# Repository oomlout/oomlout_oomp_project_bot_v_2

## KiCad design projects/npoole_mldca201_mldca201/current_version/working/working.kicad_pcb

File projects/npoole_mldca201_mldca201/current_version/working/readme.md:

# mldca201
 
## summary 
* id: npoole_mldca201_mldca201
* user: npoole
* name: mldca201
* board: mldca201
* repo: https://github.com/NPoole/MLDCA201

* src_file_repo_sch: 
* src_file_repo_sch_link: https://github.com/NPoole/MLDCA201/tree/main/
* full details link: https://github.com/oomlout/oomlout_oomp_project_bot_v_2/tree/main/projects/npoole_mldca201_mldca201/current_version/working  

## schematic  
  
[schematic (pdf)](working_schematic.pdf) 

## pcb  

[board (pdf)](working.pdf)  

## working_bom
| Id | Designator | Footprint | Quantity | Designation | Supplier and ref |  | None | 
| --- | --- | --- | --- | --- | --- | --- | --- | 
| 1 | R35,R36,R37,R34 | 0603 | 4 | 5.1k |  |  | [''] | 
| 2 | R14,R31,R28,R25,R26,R24,R15,R27,R29,R30 | 0603 | 10 | 10k |  |  | [''] | 
| 3 | C5,C4 | 0603 | 2 | 1.0uF |  |  | [''] | 
| 4 | S19,S5,S12,S6,S4,S15,S11,S1,S22,S7,S8,S9,S14,S16,S13,S2,S18,S10,S21,S3,S17,S23,S20,S24 | CHERRY-MX-LED-1U | 24 | MECHANICAL-KEYBOARD1U |  |  | [''] | 
| 5 | D21,D2,D1,D17,D32,D15,D33,D20,D18,D16,D29,D24,D12,D9,D10,D3,D19,D34,D5,D13,D6,D11,D22,D4,D14,D8,D7,D23 | SOD-323@1 | 28 | 250mA/100V |  |  | [''] | 
| 6 | C2,C1,C3 | 0805 | 3 | 22uF |  |  | [''] | 
| 7 | U5 | QFN-44-NOPAD_1_1-LESS_PASTE | 1 | 32U4 |  |  | [''] | 
| 8 | D28,D27,D25,D26 | LED-0603@1 | 4 | RED |  |  | [''] | 
| 9 | @HOLE0 |  | 1 |  |  |  | [''] | 
| 10 | R19,R23,R17,R22,R20,R16,R18,R21 | 0603 | 8 | 20k |  |  | [''] | 
| 11 | C15,C11,C8,C16 | 0603 | 4 | 22pF |  |  | [''] | 
| 12 | R13,R1,R3 | 0603 | 3 | 100k |  |  | [''] | 
| 13 | C14 | PANASONIC_D | 1 | 100uF |  |  | [''] | 
| 14 | U$1 | ICP-10101 | 1 | ICP-10101 |  |  | [''] | 
| 15 | U2 | MSOP8 | 1 | PAM2401 |  |  | [''] | 
| 16 | U7 | SO14 | 1 | LMV324 |  |  | [''] | 
| 17 | R5,R10,R8,R7 | 0603 | 4 | 2.2k |  |  | [''] | 
| 18 | C13,C7 | 0603 | 2 | 0.1uF |  |  | [''] | 
| 19 | S28,S26,S27,S25 | TACTILE_SWITCH_SMD_5.2MM | 4 | MOMENTARY-SWITCH-SPST-SMD-5.2MM-TALL |  |  | [''] | 
| 20 | R4,R2 | 0603 | 2 | 750K |  |  | [''] | 
| 21 | R33 | 0603 | 1 | 10 |  |  | [''] | 
| 22 | D35,D31 | SOD-323 | 2 | 3A/10V/280mV |  |  | [''] | 
| 23 | C6 | 0603 | 1 | 100pF |  |  | [''] | 
| 24 | R32,R12,R9 | 0603 | 3 | 1k |  |  | [''] | 
| 25 | Y1,Y2 | CRYSTAL-SMD-2.0X1.6MM | 2 | 16MHz |  |  | [''] | 
| 26 | U1 | SOT23-5 | 1 | MCP73831 |  |  | [''] | 
| 27 | J7 | AUDIO-JACK | 1 | AUDIO_JACK_3.5MM_PTH |  |  | [''] | 
| 28 | U4 | VSSOP_8PIN | 1 |  |  |  | [''] | 
| 29 | L1 | INDUCTOR_4X4MM | 1 | 2.2UH3A |  |  | [''] | 
| 30 | C12 | 0603 | 1 | 10nF |  |  | [''] | 
| 31 | Q1 | SOT-416FL | 1 | 100mA/20V/3.8Î© |  |  | [''] | 
| 32 | C10,C9 | 0603 | 2 | 4.7uF |  |  | [''] | 
| 33 | RPROG0 | 0603 | 1 | 2.0k |  |  | [''] | 
| 34 | D30 | LED-0603@1 | 1 | BLUE |  |  | [''] | 
| 35 | J4,J2 | JST-2-SMD | 2 | JST |  |  | [''] | 
| 36 | VR1 | SLIDER-SMALL | 1 | 10k |  |  | [''] | 
| 37 | J6 | USB-C-16P-2LAYER-PADS | 1 |  |  |  | [''] | 
| 38 | FRAME1 | CREATIVE_COMMONS | 1 | FRAME-LEDGER |  |  | [''] | 
| 39 | U3 | SOT23-5 | 1 | AP2127K-1.8V |  |  | [''] | 
| 40 | R6 | 0603 | 1 | 330 |  |  | [''] | 
| 41 | S31 | SWITCH_SPST_SMD_A | 1 |  |  |  | [''] | 
| 42 | U6 | 32M1-A_ATM | 1 | ATTINY861V-10MU |  |  | [''] | 
| 43 | R11 | 0603 | 1 | 200k |  |  | [''] | 
| 44 | J3,J5 | 2X3-NS | 2 | AVR_SPI_PROG_3X2NS |  |  | [''] | 

## bom_schematic
| Ref | Qnty | Value | Cmp name | Footprint | Description | Vendor | DNP | 
| --- | --- | --- | --- | --- | --- | --- | --- | 
| C1, C2, C3 | 3 | 22UF-0805-6.3V-20% | 22UF-0805-6.3V-20% | working:0805 |  |  |  | 
| C4, C5 | 2 | 1.0UF-0603-16V-10% | 1.0UF-0603-16V-10% | working:0603 |  |  |  | 
| C6 | 1 | 100PF-0603-50V-5% | 100PF-0603-50V-5% | working:0603 |  |  |  | 
| C7, C13 | 2 | 0.1UF-0603-25V-(+80/-20%) | 0.1UF-0603-25V-(+80/-20%) | working:0603 |  |  |  | 
| C8, C11, C15, C16 | 4 | 22PF-0603-50V-5% | 22PF-0603-50V-5% | working:0603 |  |  |  | 
| C9, C10 | 2 | 4.7UF-0603-35V-(20%) | 4.7UF-0603-35V-(20%) | working:0603 |  |  |  | 
| C12 | 1 | 10NF-0603-50V-10% | 10NF-0603-50V-10% | working:0603 |  |  |  | 
| C14 | 1 | 100UF-POLAR-25V-20%(ELEC) | 100UF-POLAR-25V-20%(ELEC) | working:PANASONIC_D |  |  |  | 
| D1, D2, D3, D4, D5, D6, D7, D8, D9, D10, D11, D12, D13, D14, D15, D16, D17, D18, D19, D20, D21, D22, D23, D24, D29, D32, D33, D34 | 28 | DIODE-BAS16J | DIODE-BAS16J | working:SOD-323@1 |  |  |  | 
| D25, D26, D27, D28 | 4 | RED | LED-RED0603 | working:LED-0603@1 |  |  |  | 
| D30 | 1 | BLUE | LED-BLUE0603 | working:LED-0603@1 |  |  |  | 
| D31, D35 | 2 | 3A/10V/280mV | DIODE-SCHOTTKY-BAT60A | working:SOD-323 |  |  |  | 
| FRAME1 | 1 | FRAME-LEDGER | FRAME-LEDGER | working:CREATIVE_COMMONS |  |  |  | 
| J2, J4 | 2 | JST | CONN_02-JST-2MM-SMT | working:JST-2-SMD |  |  |  | 
| J3, J5 | 2 | AVR_SPI_PROG_3X2NS | AVR_SPI_PROG_3X2NS | working:2X3-NS |  |  |  | 
| J6 | 1 | USB_C_2-LAYER_PADS | USB_C_2-LAYER_PADS | working:USB-C-16P-2LAYER-PADS |  |  |  | 
| J7 | 1 | AUDIO_JACK_3.5MM_PTH | AUDIO_JACK_3.5MM_PTH | working:AUDIO-JACK |  |  |  | 
| L1 | 1 | INDUCTOR-IFSC1515AHER2R2M01 | INDUCTOR-IFSC1515AHER2R2M01 | working:INDUCTOR_4X4MM |  |  |  | 
| Q1 | 1 | MOSFET_PCH-RE1C001ZPTL | MOSFET_PCH-RE1C001ZPTL | working:SOT-416FL |  |  |  | 
| R1, R3, R13 | 3 | 100KOHM-0603-1/10W-1% | 100KOHM-0603-1/10W-1% | working:0603 |  |  |  | 
| R2, R4 | 2 | 750KOHM-0603-1/10W-1% | 750KOHM-0603-1/10W-1% | working:0603 |  |  |  | 
| R5, R7, R8, R10 | 4 | 2.2KOHM-0603-1/10W-1% | 2.2KOHM-0603-1/10W-1% | working:0603 |  |  |  | 
| R6 | 1 | 330OHM-0603-1/10W-1% | 330OHM-0603-1/10W-1% | working:0603 |  |  |  | 
| R9, R12, R32 | 3 | 1KOHM-0603-1/10W-1% | 1KOHM-0603-1/10W-1% | working:0603 |  |  |  | 
| R11 | 1 | 200KOHM-0603-1/10W-1% | 200KOHM-0603-1/10W-1% | working:0603 |  |  |  | 
| R14, R15, R24, R25, R26, R27, R28, R29, R30, R31 | 10 | 10KOHM-0603-1/10W-1% | 10KOHM-0603-1/10W-1% | working:0603 |  |  |  | 
| R16, R17, R18, R19, R20, R21, R22, R23 | 8 | 20KOHM-0603-1/10W-1% | 20KOHM-0603-1/10W-1% | working:0603 |  |  |  | 
| R33 | 1 | 10OHM-0603-1/10W-1% | 10OHM-0603-1/10W-1% | working:0603 |  |  |  | 
| R34, R35, R36, R37 | 4 | 5.1k | 5.1KOHM5.1KOHM-0603-1/10W-1% | working:0603 |  |  |  | 
| RPROG0 | 1 | 2.0KOHM-0603-1/10W-5% | 2.0KOHM-0603-1/10W-5% | working:0603 |  |  |  | 
| S1, S2, S3, S4, S5, S6, S7, S8, S9, S10, S11, S12, S13, S14, S15, S16, S17, S18, S19, S20, S21, S22, S23, S24 | 24 | MECHANICAL-KEYBOARD1U | MECHANICAL-KEYBOARD1U | working:CHERRY-MX-LED-1U |  |  |  | 
| S25, S26, S27, S28 | 4 | MOMENTARY-SWITCH-SPST-SMD-5.2MM-TALL | MOMENTARY-SWITCH-SPST-SMD-5.2MM-TALL | working:TACTILE_SWITCH_SMD_5.2MM |  |  |  | 
| S31 | 1 | SWITCH-SPDT-SMD-RIGHT-ANGLE | SWITCH-SPDT-SMD-RIGHT-ANGLE | working:SWITCH_SPST_SMD_A |  |  |  | 
| U1 | 1 | MCP73831 | MCP73831 | working:SOT23-5 |  |  |  | 
| U2 | 1 | PAM2401 | PAM2401 | working:MSOP8 |  |  |  | 
| U3 | 1 | V_REG_AP2127K-1.8V | V_REG_AP2127K-1.8V | working:SOT23-5 |  |  |  | 
| U4 | 1 | PCA9306VSSOP_8PIN | PCA9306VSSOP_8PIN | working:VSSOP_8PIN |  |  |  | 
| U5 | 1 | ATMEGA32U41:1-LESS_PASTE | ATMEGA32U41{colon}1-LESS_PASTE | working:QFN-44-NOPAD_1_1-LESS_PASTE |  |  |  | 
| U6 | 1 | ATTINY861V-10MU | ATTINY861V-10MU | working:32M1-A_ATM |  |  |  | 
| U7 | 1 | LMV324 | LMV324 | working:SO14 |  |  |  | 
| U$1 | 1 | ICP-10101 | ICP-10101 | working:ICP-10101 |  |  |  | 
| VR1 | 1 | 10k | POTENTIOMETER_SLIDE-20MM-1/10W-20% | working:SLIDER-SMALL |  |  |  | 
| Y1, Y2 | 2 | 16MHz | CRYSTAL-16MHZSMD-2X1.6 | working:CRYSTAL-SMD-2.0X1.6MM |  |  |  |

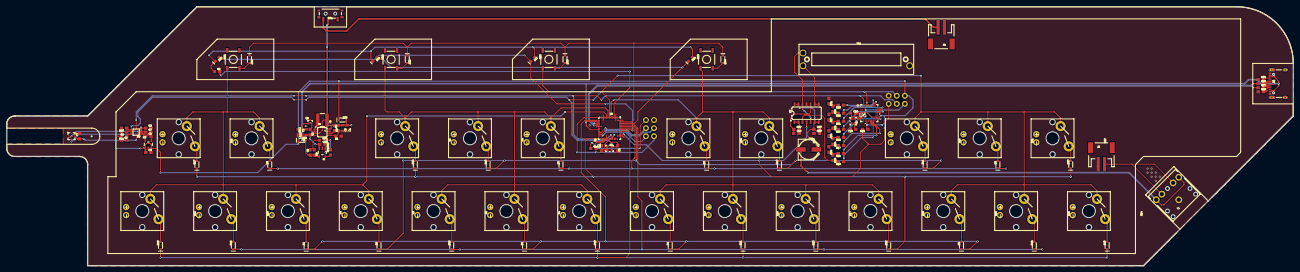
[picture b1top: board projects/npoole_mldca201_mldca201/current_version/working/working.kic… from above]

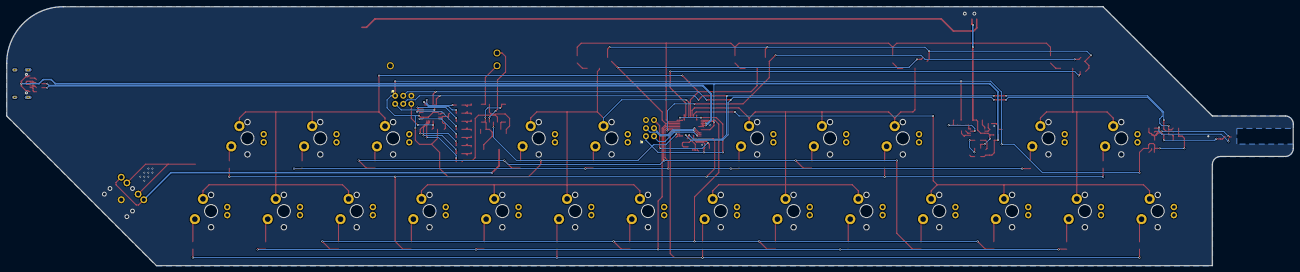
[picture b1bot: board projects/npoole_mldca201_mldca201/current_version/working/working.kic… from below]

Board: 2 copper layers, 403.9 x 81.3 mm, 139 parts (2 on the bottom side), 103 nets.

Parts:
@HOLE0: (no value)
C1, C2, C3: 22uF; 0805
C4, C5: 1.0uF; 0603
C6: 100pF; 0603
C7, C13: 0.1uF; 0603
C8, C11, C15, C16: 22pF; 0603
C9, C10: 4.7uF; 0603
C12: 10nF; 0603
C14: 100uF; PANASONIC_D
D1, D2, D3, D4, D5, D6, D7, D8, D9, D10, D11, D12, D13, D14, D15, D16, D17, D18, D19, D20, D21, D22, D23, D24, D29, D32, D33, D34: 250mA/100V; SOD-323@1
D25, D26, D27, D28: RED; LED-0603@1
D30: BLUE; LED-0603@1
D31, D35: 3A/10V/280mV; SOD-323
FRAME1: FRAME-LEDGER; CREATIVE_COMMONS
J2, J4: JST; JST-2-SMD
J3, J5: AVR_SPI_PROG_3X2NS; 2X3-NS
J6: USB-C-16P-2LAYER-PADS
J7: AUDIO_JACK_3.5MM_PTH; AUDIO-JACK
L1: 2.2UH3A; INDUCTOR_4X4MM
Q1: 100mA/20V/3.8Ω; SOT-416FL
R1, R3, R13: 100k; 0603
R2, R4: 750K; 0603
R5, R7, R8, R10: 2.2k; 0603
R6: 330; 0603
R9, R12, R32: 1k; 0603
R11: 200k; 0603
R14, R15, R24, R25, R26, R27, R28, R29, R30, R31: 10k; 0603
R16, R17, R18, R19, R20, R21, R22, R23: 20k; 0603
R33: 10; 0603
R34, R35, R36, R37: 5.1k; 0603
RPROG0: 2.0k; 0603
S1, S2, S3, S4, S5, S6, S7, S8, S9, S10, S11, S12, S13, S14, S15, S16, S17, S18, S19, S20, S21, S22, S23, S24: MECHANICAL-KEYBOARD1U; CHERRY-MX-LED-1U
S25, S26, S27, S28: MOMENTARY-SWITCH-SPST-SMD-5.2MM-TALL; TACTILE_SWITCH_SMD_5.2MM
S31: SWITCH_SPST_SMD_A
U1: MCP73831; SOT23-5
U2: PAM2401; MSOP8
U3: AP2127K-1.8V; SOT23-5
U4: VSSOP_8PIN
U5: 32U4; QFN-44-NOPAD_1_1-LESS_PASTE
U6: ATTINY861V-10MU; 32M1-A_ATM
U7: LMV324; SO14
U$1: ICP-10101
VR1: 10k; SLIDER-SMALL
Y1, Y2: 16MHz; CRYSTAL-SMD-2.0X1.6MM

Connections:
1.8V: C5.1, C7.1, R5.2, R7.2, U3.5, U4.P2, U$1.5, U$1.6, U$1.10
5V: C4.1, D31.C, D35.C, J3.2, J5.2, R8.2, R10.2, R11.2, R14.2, R15.2, U3.1, U3.3, U5.14, U5.24, U5.34, U5.44, U6.4, U6.18, U7.4
32U4_CIPO: J5.1, U5.11
32U4_COPI: J5.4, U5.10
32U4_SCK: J5.3, U5.9
861CIPO: J3.1, U6.31
AUDIO_OUT: C14.-, J7.RING, J7.TIP
COL1: D1.C, D2.C, D3.C, D4.C, U5.1
COL2: D5.C, D6.C, D7.C, D8.C, U5.28
COL3: D9.C, D10.C, D11.C, D12.C, U5.29
COL4: D13.C, D14.C, D15.C, D16.C, U5.30
COL5: D17.C, D22.C, D23.C, D24.C, U5.12
COL6: D18.C, D19.C, D20.C, D21.C, U5.26
COL7: D29.C, D32.C, D33.C, D34.C, U5.32
DAC_0: R23.1, U6.26
DAC_1: R22.1, U6.25
DAC_2: R21.1, U6.23
DAC_3: R20.1, U6.22
DAC_4: R18.1, U6.17
DAC_5: R17.1, U6.15
DAC_6: R16.1, U6.14
DAC_7: R19.1, U6.13
DAC_OUT: R19.2, R29.2, U7.3
EN: Q1.2, R2.1, U2.2
GND: C1.2, C2.2, C3.2, C4.2, C5.2, C6.1, C7.2, C8.2, C9.2, C10.2, C11.2, C12.2, C15.2, C16.2, J2.1, J3.6, J4.1, J5.6, J6.GND, J6.GND2, J7.SLEEVE, Q1.3, R1.1, R3.1, R13.2, R31.1, R33.1, R34.1, R35.1, RPROG0.2, U1.2, U2.4, U2.8, U3.2, U4.P1, U5.5, U5.15, U5.23, U5.33, U5.35, U5.43, U6.5, U6.21, U7.11, U$1.3, U$1.8, U$1.9, VR1.BOTTOM
LED0: R6.2, U5.36
LED1: D26.A, D28.C, U5.31
LED2: D25.A, D27.C, U5.27
unnamed: RPROG0.1, U1.5
unnamed: D30.C, U1.1
unnamed: J4.2, S31.1
unnamed: D30.A, R9.1
unnamed: D1.A, S8.S2
unnamed: D2.A, S1.S2
unnamed: D3.A, S20.S2
unnamed: D4.A, S13.S2
unnamed: D5.A, S14.S2
unnamed: D6.A, S21.S2
unnamed: D7.A, S2.S2
unnamed: D8.A, S9.S2
unnamed: D9.A, S3.S2
unnamed: D10.A, S4.S2
unnamed: D11.A, S15.S2
unnamed: D12.A, S16.S2
unnamed: D13.A, S17.S2
unnamed: D14.A, S22.S2
unnamed: D15.A, S5.S2
unnamed: D16.A, S10.S2
unnamed: D17.A, S11.S2
unnamed: D24.A, S6.S2
unnamed: D23.A, S23.S2
unnamed: D22.A, S18.S2
unnamed: D21.A, S19.S2
unnamed: D20.A, S24.S2
unnamed: D19.A, S7.S2
unnamed: D18.A, S12.S2
unnamed: R1.2, R4.1, U2.5
unnamed: L1.P$2, U2.1
unnamed: R3.2, U2.6
unnamed: D29.A, S25.3
unnamed: D32.A, S26.3
unnamed: Q1.1, R12.2, R13.1
unnamed: D33.A, S27.3
unnamed: D34.A, S28.3
unnamed: D25.C, D26.C, D27.A, D28.A, R6.1
unnamed: C6.2, R11.1, U4.P7, U4.P8
unnamed: C1.1, C2.1, D35.A, R4.2, U2.7
unnamed: C11.1, U5.16, Y2.1
unnamed: C8.1, U5.17, Y2.3
unnamed: U7.8, U7.9, VR1.TOP
unnamed: R16.2, R28.2, R29.1
unnamed: R17.2, R24.2, R28.1
unnamed: R18.2, R24.1, R25.2
unnamed: R20.2, R25.1, R26.2
unnamed: R21.2, R26.1, R27.2
unnamed: R22.2, R27.1, R30.2
unnamed: R23.2, R30.1, R31.2
unnamed: R32.2, U7.1, U7.2
unnamed: C12.1, R32.1, U7.10
unnamed: U7.5, U7.12, VR1.WIPER
unnamed: C13.1, C14.+, U7.6, U7.7, U7.13, U7.14
unnamed: C13.2, R33.2
unnamed: J6.A5, R35.2
unnamed: J6.B5, R34.2
unnamed: J6.A6, J6.B6, R36.2
unnamed: J6.A7, J6.B7, R37.2
unnamed: C16.1, U6.7, Y1.1
unnamed: C15.1, U6.8, Y1.3
unnamed: J2.2, J7.RSH, J7.TSH
ROW1: S3.S1, S8.S1, S9.S1, S10.S1, S11.S1, S12.S1, S25.1, U5.41
ROW2: S1.S1, S2.S1, S4.S1, S5.S1, S6.S1, S7.S1, S26.1, U5.40
ROW3: S15.S1, S20.S1, S21.S1, S22.S1, S23.S1, S24.S1, S27.1, U5.39
ROW4: S13.S1, S14.S1, S16.S1, S17.S1, S18.S1, S19.S1, S28.1, U5.38
SCL1_8: R7.1, U4.P3, U$1.2
SCL5: J3.3, R8.1, U4.P6, U5.18, U6.32
SDA1_8: R5.1, U4.P4, U$1.4
SDA5: J3.4, R10.1, U4.P5, U5.19, U6.30
USB_N: R37.1, U5.3
USB_P: R36.1, U5.4
VBATT: C3.1, C10.1, L1.P$1, R2.2, S31.2, U1.3, U2.3
VUSB: C9.1, D31.A, J6.VBUS1, J6.VBUS2, R9.2, R12.1, U1.4, U5.2, U5.7
~32U4_RESET: J5.5, R14.1, U5.13
~861RESET: J3.5, R15.1, U6.11

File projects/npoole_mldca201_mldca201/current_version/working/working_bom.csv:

"Id";"Designator";"Footprint";"Quantity";"Designation";"Supplier and ref";
1;"R35,R36,R37,R34";"0603";4;"5.1k";;;
2;"R14,R31,R28,R25,R26,R24,R15,R27,R29,R30";"0603";10;"10k";;;
3;"C5,C4";"0603";2;"1.0uF";;;
4;"S19,S5,S12,S6,S4,S15,S11,S1,S22,S7,S8,S9,S14,S16,S13,S2,S18,S10,S21,S3,S17,S23,S20,S24";"CHERRY-MX-LED-1U";24;"MECHANICAL-KEYBOARD1U";;;
5;"D21,D2,D1,D17,D32,D15,D33,D20,D18,D16,D29,D24,D12,D9,D10,D3,D19,D34,D5,D13,D6,D11,D22,D4,D14,D8,D7,D23";"SOD-323@1";28;"250mA/100V";;;
6;"C2,C1,C3";"0805";3;"22uF";;;
7;"U5";"QFN-44-NOPAD_1_1-LESS_PASTE";1;"32U4";;;
8;"D28,D27,D25,D26";"LED-0603@1";4;"RED";;;
9;"@HOLE0";"";1;"";;;
10;"R19,R23,R17,R22,R20,R16,R18,R21";"0603";8;"20k";;;
11;"C15,C11,C8,C16";"0603";4;"22pF";;;
12;"R13,R1,R3";"0603";3;"100k";;;
13;"C14";"PANASONIC_D";1;"100uF";;;
14;"U$1";"ICP-10101";1;"ICP-10101";;;
15;"U2";"MSOP8";1;"PAM2401";;;
16;"U7";"SO14";1;"LMV324";;;
17;"R5,R10,R8,R7";"0603";4;"2.2k";;;
18;"C13,C7";"0603";2;"0.1uF";;;
19;"S28,S26,S27,S25";"TACTILE_SWITCH_SMD_5.2MM";4;"MOMENTARY-SWITCH-SPST-SMD-5.2MM-TALL";;;
20;"R4,R2";"0603";2;"750K";;;
21;"R33";"0603";1;"10";;;
22;"D35,D31";"SOD-323";2;"3A/10V/280mV";;;
23;"C6";"0603";1;"100pF";;;
24;"R32,R12,R9";"0603";3;"1k";;;
25;"Y1,Y2";"CRYSTAL-SMD-2.0X1.6MM";2;"16MHz";;;
26;"U1";"SOT23-5";1;"MCP73831";;;
27;"J7";"AUDIO-JACK";1;"AUDIO_JACK_3.5MM_PTH";;;
28;"U4";"VSSOP_8PIN";1;"";;;
29;"L1";"INDUCTOR_4X4MM";1;"2.2UH3A";;;
30;"C12";"0603";1;"10nF";;;
31;"Q1";"SOT-416FL";1;"100mA/20V/3.8Ω";;;
32;"C10,C9";"0603";2;"4.7uF";;;
33;"RPROG0";"0603";1;"2.0k";;;
34;"D30";"LED-0603@1";1;"BLUE";;;
35;"J4,J2";"JST-2-SMD";2;"JST";;;
36;"VR1";"SLIDER-SMALL";1;"10k";;;
37;"J6";"USB-C-16P-2LAYER-PADS";1;"";;;
38;"FRAME1";"CREATIVE_COMMONS";1;"FRAME-LEDGER";;;
39;"U3";"SOT23-5";1;"AP2127K-1.8V";;;
40;"R6";"0603";1;"330";;;
41;"S31";"SWITCH_SPST_SMD_A";1;"";;;
42;"U6";"32M1-A_ATM";1;"ATTINY861V-10MU";;;
43;"R11";"0603";1;"200k";;;
44;"J3,J5";"2X3-NS";2;"AVR_SPI_PROG_3X2NS";;;

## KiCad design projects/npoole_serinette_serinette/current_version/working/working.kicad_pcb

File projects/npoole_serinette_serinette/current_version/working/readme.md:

# serinette
 
## summary 
* id: npoole_serinette_serinette
* user: npoole
* name: serinette
* board: serinette
* repo: https://github.com/NPoole/Serinette

* src_file_repo_sch: 
* src_file_repo_sch_link: https://github.com/NPoole/Serinette/tree/main/
* full details link: https://github.com/oomlout/oomlout_oomp_project_bot_v_2/tree/main/projects/npoole_serinette_serinette/current_version/working  

## schematic  
  
[schematic (pdf)](working_schematic.pdf) 

## pcb  

[board (pdf)](working.pdf)  

## working_bom
| Id | Designator | Footprint | Quantity | Designation | Supplier and ref |  | None | 
| --- | --- | --- | --- | --- | --- | --- | --- | 
| 1 | U15,U13,U9,U2,U3,U7,U1,U6,U11,U4,U5,U10,U8,U14,U12 | ALS-PT19 | 15 | LIGHT_SENSORALS |  |  | [''] | 
| 2 | S3,S2,S1,S4 | TACTILE_SWITCH_SMD_5.2MM | 4 | MOMENTARY-SWITCH-SPST-SMD-5.2MM-TALL |  |  | [''] | 
| 3 | C3,C6 | 0603 | 2 | 4.7uF |  |  | [''] | 
| 4 | @HOLE5,@HOLE2,@HOLE3,@HOLE14,@HOLE7,@HOLE8,@HOLE11,@HOLE6,@HOLE1,@HOLE0,@HOLE4,@HOLE9,@HOLE12,@HOLE13,@HOLE10 |  | 15 |  |  |  | [''] | 
| 5 | LS1 | BUZZER_SMD | 1 | BUZZER-SMD-SQUARE |  |  | [''] | 
| 6 | C1,C2 | 0603 | 2 | 1.0uF |  |  | [''] | 
| 7 | R17 | 0603 | 1 | 10k |  |  | [''] | 
| 8 | C5 | 0603 | 1 | 2.2uF |  |  | [''] | 
| 9 | C4 | 0603 | 1 | 0.1uF |  |  | [''] | 
| 10 | E$1 | KIKKERLAND15 | 1 |  |  |  | [''] | 
| 11 | OLED1 | OLED-UG-2832TSWGG01-REAR | 1 | 32x128 OLED |  |  | [''] | 
| 12 | R16 | 0603 | 1 | 560K |  |  | [''] | 
| 13 | J1 | USB-C-16P-2LAYER-PADS | 1 |  |  |  | [''] | 
| 14 | FRAME1 | CREATIVE_COMMONS | 1 | FRAME-LETTER |  |  | [''] | 
| 15 | D6,D2,D12,D4,D10,D15,D5,D11,D8,D3,D9,D14,D1,D7,D13 | LED-0603 | 15 |  |  |  | [''] | 
| 16 | R13,R8,R11,R3,R5,R4,R15,R9,R2,R1,R7,R10,R6,R14,R12 | 0603 | 15 | 330 |  |  | [''] | 

## bom_schematic
| Ref | Qnty | Value | Cmp name | Footprint | Description | Vendor | DNP | 
| --- | --- | --- | --- | --- | --- | --- | --- | 
| C1, C2 | 2 | 1.0UF-0603-16V-10% | 1.0UF-0603-16V-10% | working:0603 |  |  |  | 
| C3, C6 | 2 | 4.7UF-0603-35V-(20%) | 4.7UF-0603-35V-(20%) | working:0603 |  |  |  | 
| C4 | 1 | 0.1UF-0603-100V-10% | 0.1UF-0603-100V-10% | working:0603 |  |  |  | 
| C5 | 1 | 2.2UF-0603-10V-20% | 2.2UF-0603-10V-20% | working:0603 |  |  |  | 
| D1, D2, D3, D4, D5, D6, D7, D8, D9, D10, D11, D12, D13, D14, D15 | 15 | LED0603 | LED0603 | working:LED-0603 |  |  |  | 
| FRAME1 | 1 | FRAME-LETTER | FRAME-LETTER | working:CREATIVE_COMMONS |  |  |  | 
| J1 | 1 | USB_C_2-LAYER_PADS | USB_C_2-LAYER_PADS | working:USB-C-16P-2LAYER-PADS |  |  |  | 
| LS1 | 1 | BUZZER-SMD-SQUARE | BUZZER-SMD-SQUARE | working:BUZZER_SMD |  |  |  | 
| OLED1 | 1 | OLED128X64SIDEREAR-MOUNT | OLED128X64SIDEREAR-MOUNT | working:OLED-UG-2832TSWGG01-REAR |  |  |  | 
| R1, R2, R3, R4, R5, R6, R7, R8, R9, R10, R11, R12, R13, R14, R15 | 15 | 330OHM-0603-1/10W-1% | 330OHM-0603-1/10W-1% | working:0603 |  |  |  | 
| R16 | 1 | 750KOHM-0603-1/10W-1% | 750KOHM-0603-1/10W-1% | working:0603 |  |  |  | 
| R17 | 1 | 10KOHM-0603-1/10W-1% | 10KOHM-0603-1/10W-1% | working:0603 |  |  |  | 
| S1, S2, S3, S4 | 4 | MOMENTARY-SWITCH-SPST-SMD-5.2MM-TALL | MOMENTARY-SWITCH-SPST-SMD-5.2MM-TALL | working:TACTILE_SWITCH_SMD_5.2MM |  |  |  | 
| U1, U2, U3, U4, U5, U6, U7, U8, U9, U10, U11, U12, U13, U14, U15 | 15 | LIGHT_SENSORALS | LIGHT_SENSORALS | working:ALS-PT19 |  |  |  | 
| U16 | 1 | ATMEGA32U4-ARDUINO1:1-LESS_PASTE | ATMEGA32U4-ARDUINO1{colon}1-LESS_PASTE | working:QFN-44-NOPAD_1_1-LESS_PASTE |  |  |  |

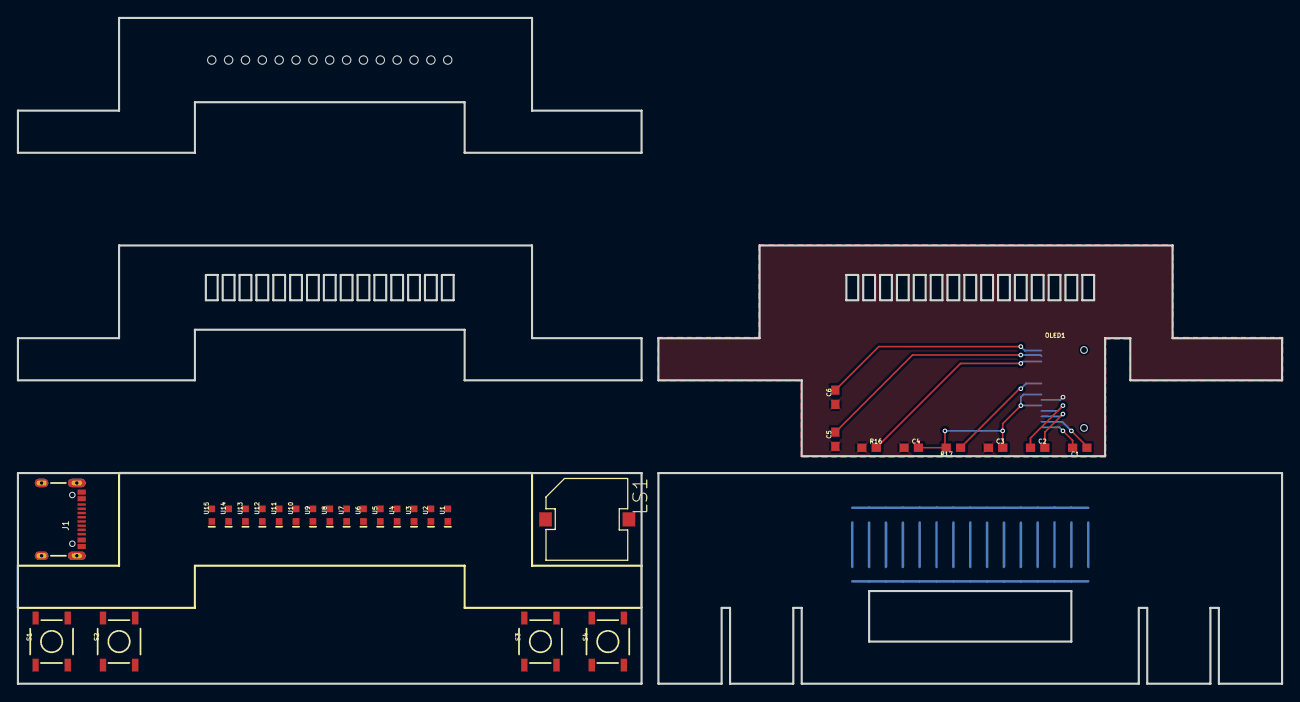
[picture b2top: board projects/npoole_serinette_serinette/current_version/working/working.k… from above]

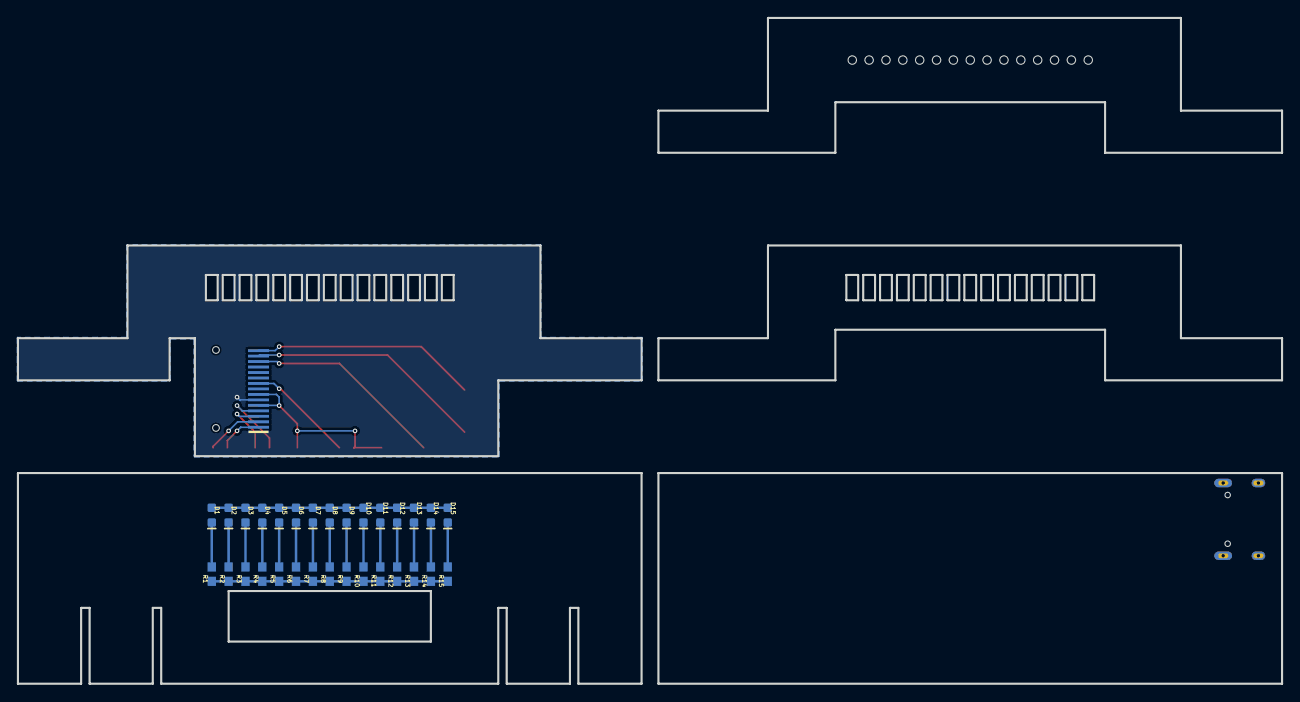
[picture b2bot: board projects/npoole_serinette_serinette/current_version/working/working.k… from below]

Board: 2 copper layers, 150.0 x 79.0 mm, 77 parts (30 on the bottom side), 27 nets.

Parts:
@HOLE0, @HOLE1, @HOLE2, @HOLE3, @HOLE4, @HOLE5, @HOLE6, @HOLE7, @HOLE8, @HOLE9, @HOLE10, @HOLE11, @HOLE12, @HOLE13, @HOLE14: (no value)
C1, C2: 1.0uF; 0603
C3, C6: 4.7uF; 0603
C4: 0.1uF; 0603
C5: 2.2uF; 0603
D1, D2, D3, D4, D5, D6, D7, D8, D9, D10, D11, D12, D13, D14, D15: LED-0603
E$1: KIKKERLAND15
FRAME1: FRAME-LETTER; CREATIVE_COMMONS
J1: USB-C-16P-2LAYER-PADS
LS1: BUZZER-SMD-SQUARE; BUZZER_SMD
OLED1: 32x128 OLED; OLED-UG-2832TSWGG01-REAR
R1, R2, R3, R4, R5, R6, R7, R8, R9, R10, R11, R12, R13, R14, R15: 330; 0603
R16: 560K; 0603
R17: 10k; 0603
S1, S2, S3, S4: MOMENTARY-SWITCH-SPST-SMD-5.2MM-TALL; TACTILE_SWITCH_SMD_5.2MM
U1, U2, U3, U4, U5, U6, U7, U8, U9, U10, U11, U12, U13, U14, U15: LIGHT_SENSORALS; ALS-PT19

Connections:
3.3V: C3.2, C4.2, OLED1.5, OLED1.7, R17.2
GND: C3.1, C4.1, C5.1, C6.1, OLED1.6, R16.1
unnamed: D1.C, R1.2
unnamed: D2.C, R2.2
unnamed: D3.C, R3.2
unnamed: D4.C, R4.2
unnamed: D5.C, R5.2
unnamed: D6.C, R6.2
unnamed: D7.C, R7.2
unnamed: D8.C, R8.2
unnamed: D9.C, R9.2
unnamed: D10.C, R10.2
unnamed: D11.C, R11.2
unnamed: D12.C, R12.2
unnamed: D13.C, R13.2
unnamed: D14.C, R14.2
unnamed: D15.C, R15.2
unnamed: R1.1, R2.1, R3.1, R4.1, R5.1, R6.1, R7.1, R8.1, R9.1, R10.1, R11.1, R12.1, R13.1, R14.1, R15.1
unnamed: D1.A, D2.A, D3.A, D4.A, D5.A, D6.A, D7.A, D8.A, D9.A, D10.A, D11.A, D12.A, D13.A, D14.A, D15.A
unnamed: C1.2, OLED1.1
unnamed: C2.2, OLED1.3
unnamed: C1.1, OLED1.2
unnamed: C2.1, OLED1.4
unnamed: OLED1.13, R16.2
unnamed: C5.2, OLED1.14
unnamed: C6.2, OLED1.15
OLED_RST: OLED1.9, R17.1

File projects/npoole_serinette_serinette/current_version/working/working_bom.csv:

"Id";"Designator";"Footprint";"Quantity";"Designation";"Supplier and ref";
1;"U15,U13,U9,U2,U3,U7,U1,U6,U11,U4,U5,U10,U8,U14,U12";"ALS-PT19";15;"LIGHT_SENSORALS";;;
2;"S3,S2,S1,S4";"TACTILE_SWITCH_SMD_5.2MM";4;"MOMENTARY-SWITCH-SPST-SMD-5.2MM-TALL";;;
3;"C3,C6";"0603";2;"4.7uF";;;
4;"@HOLE5,@HOLE2,@HOLE3,@HOLE14,@HOLE7,@HOLE8,@HOLE11,@HOLE6,@HOLE1,@HOLE0,@HOLE4,@HOLE9,@HOLE12,@HOLE13,@HOLE10";"";15;"";;;
5;"LS1";"BUZZER_SMD";1;"BUZZER-SMD-SQUARE";;;
6;"C1,C2";"0603";2;"1.0uF";;;
7;"R17";"0603";1;"10k";;;
8;"C5";"0603";1;"2.2uF";;;
9;"C4";"0603";1;"0.1uF";;;
10;"E$1";"KIKKERLAND15";1;"";;;
11;"OLED1";"OLED-UG-2832TSWGG01-REAR";1;"32x128 OLED";;;
12;"R16";"0603";1;"560K";;;
13;"J1";"USB-C-16P-2LAYER-PADS";1;"";;;
14;"FRAME1";"CREATIVE_COMMONS";1;"FRAME-LETTER";;;
15;"D6,D2,D12,D4,D10,D15,D5,D11,D8,D3,D9,D14,D1,D7,D13";"LED-0603";15;"";;;
16;"R13,R8,R11,R3,R5,R4,R15,R9,R2,R1,R7,R10,R6,R14,R12";"0603";15;"330";;;

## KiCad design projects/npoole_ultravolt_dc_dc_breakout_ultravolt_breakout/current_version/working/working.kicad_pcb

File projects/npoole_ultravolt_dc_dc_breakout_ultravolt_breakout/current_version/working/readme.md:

# ultravolt_dc_dc_breakout
 
## summary 
* id: npoole_ultravolt_dc_dc_breakout_ultravolt_breakout
* user: npoole
* name: ultravolt_dc_dc_breakout
* board: ultravolt_breakout
* repo: https://github.com/NPoole/Ultravolt_DC-DC_Breakout

* src_file_repo_sch: 
* src_file_repo_sch_link: https://github.com/NPoole/Ultravolt_DC-DC_Breakout/tree/main/
* full details link: https://github.com/oomlout/oomlout_oomp_project_bot_v_2/tree/main/projects/npoole_ultravolt_dc_dc_breakout_ultravolt_breakout/current_version/working  

## schematic  
  
[schematic (pdf)](working_schematic.pdf) 

## pcb  

[board (pdf)](working.pdf)  

## working_bom
| Id | Designator | Footprint | Quantity | Designation | Supplier and ref |  | None | 
| --- | --- | --- | --- | --- | --- | --- | --- | 
| 1 | U$1 | ULTRAVOLT | 1 | 1A12-P4_M |  |  | [''] | 
| 2 | U$21,U$22 | #_GND_#0 | 2 |  |  |  | [''] | 
| 3 | U$12 | #_12V_IN#0 | 1 |  |  |  | [''] | 
| 4 | J3,J4 | 1X01_2MM | 2 |  |  |  | [''] | 
| 5 | U$14 | #_#5V_REF_#0 | 1 |  |  |  | [''] | 
| 6 | J2 | 1X03_NO_SILK | 1 |  |  |  | [''] | 
| 7 | U$13 | #_GND#0 | 1 |  |  |  | [''] | 
| 8 | U$20 | #_ENABLE_#0 | 1 |  |  |  | [''] | 
| 9 | U$3,U$4,U$2,U$5 | STAND-OFF | 4 |  |  |  | [''] | 
| 10 | U$7 | #_#5V_REF#0 | 1 |  |  |  | [''] | 
| 11 | U$17 | #HV_P#0 | 1 |  |  |  | [''] | 
| 12 | J1 | POWER_JACK_PTH | 1 | POWER_JACK |  |  | [''] | 
| 13 | U$8 | #_REMOTE_ADJ#0 | 1 |  |  |  | [''] | 
| 14 | U$19 | #_I_SENSE_#0 | 1 |  |  |  | [''] | 
| 15 | U$10 | #_ENABLE#0 | 1 |  |  |  | [''] | 
| 16 | U$15 | #_ADJUST_#0 | 1 |  |  |  | [''] | 
| 17 | U$11 | #_I_SENSE#0 | 1 |  |  |  | [''] | 
| 18 | U$16 | #HV_N#0 | 1 |  |  |  | [''] | 
| 19 | J5,J6 | 1X02_NO_SILK | 2 |  |  |  | [''] | 
| 20 | U$9 | #_SIGNAL_GND#0 | 1 |  |  |  | [''] | 
| 21 | U$6 | HIGH_VOLTAGE0 | 1 |  |  |  | [''] | 
| 22 | U$18 | #_REF_GND_#0 | 1 |  |  |  | [''] | 

## bom_schematic
| Ref | Qnty | Value | Cmp name | Footprint | Description | Vendor | DNP | 
| --- | --- | --- | --- | --- | --- | --- | --- | 
| J1 | 1 | POWER_JACK | POWER_JACK | working:POWER_JACK_PTH |  |  |  | 
| J2 | 1 | CONN_031X03_NO_SILK | CONN_031X03_NO_SILK | working:1X03_NO_SILK |  |  |  | 
| J3, J4 | 2 | CONN_01PTH_2MM | CONN_01PTH_2MM | working:1X01_2MM |  |  |  | 
| J5, J6 | 2 | CONN_021X02_NO_SILK | CONN_021X02_NO_SILK | working:1X02_NO_SILK |  |  |  | 
| U$1 | 1 | 1A12-P4_M | 1A12-P4_M | working:ULTRAVOLT |  |  |  |

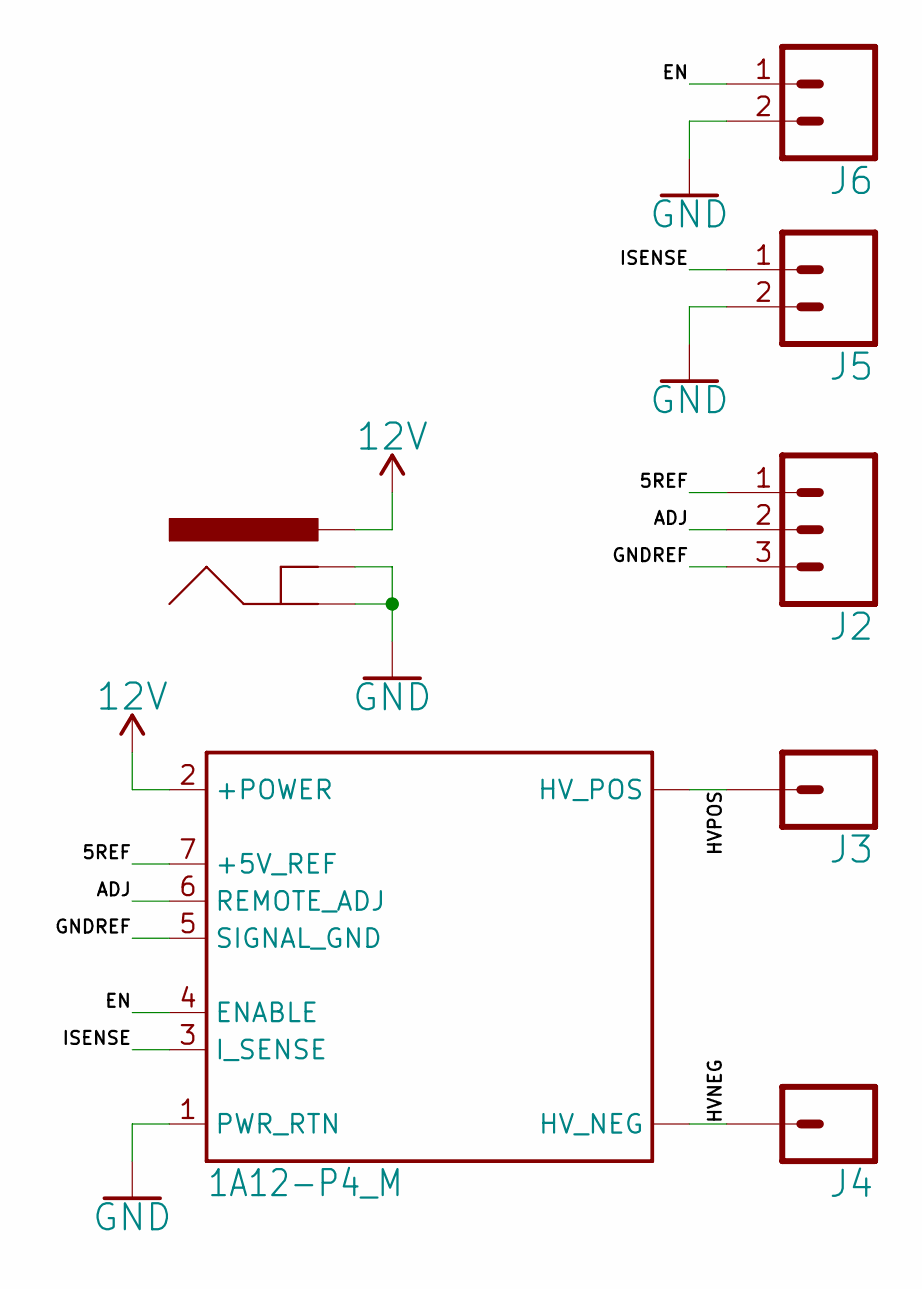
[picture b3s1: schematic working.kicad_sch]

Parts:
J1: POWER_JACK; POWER_JACK_PTH
J2: CONN_031X03_NO_SILK; 1X03_NO_SILK
J3, J4: CONN_01PTH_2MM; 1X01_2MM
J5, J6: CONN_021X02_NO_SILK; 1X02_NO_SILK
U$1: 1A12-P4_M; ULTRAVOLT

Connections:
5REF: J2.1, U$1.7 (+5V_REF)
12V: J1.PWR, U$1.2 (+POWER)
ADJ: J2.2, U$1.6 (REMOTE_ADJ)
EN: J6.1, U$1.4 (ENABLE)
GND: J1.GND, J1.GNDBREAK, J5.2, J6.2, U$1.1 (PWR_RTN)
GNDREF: J2.3, U$1.5 (SIGNAL_GND)
HVNEG: J4.1, U$1.8 (HV_NEG), U$1.9 (HV_NEG)
HVPOS: J3.1, U$1.10 (HV_POS), U$1.11 (HV_POS)
ISENSE: J5.1, U$1.3 (I_SENSE)

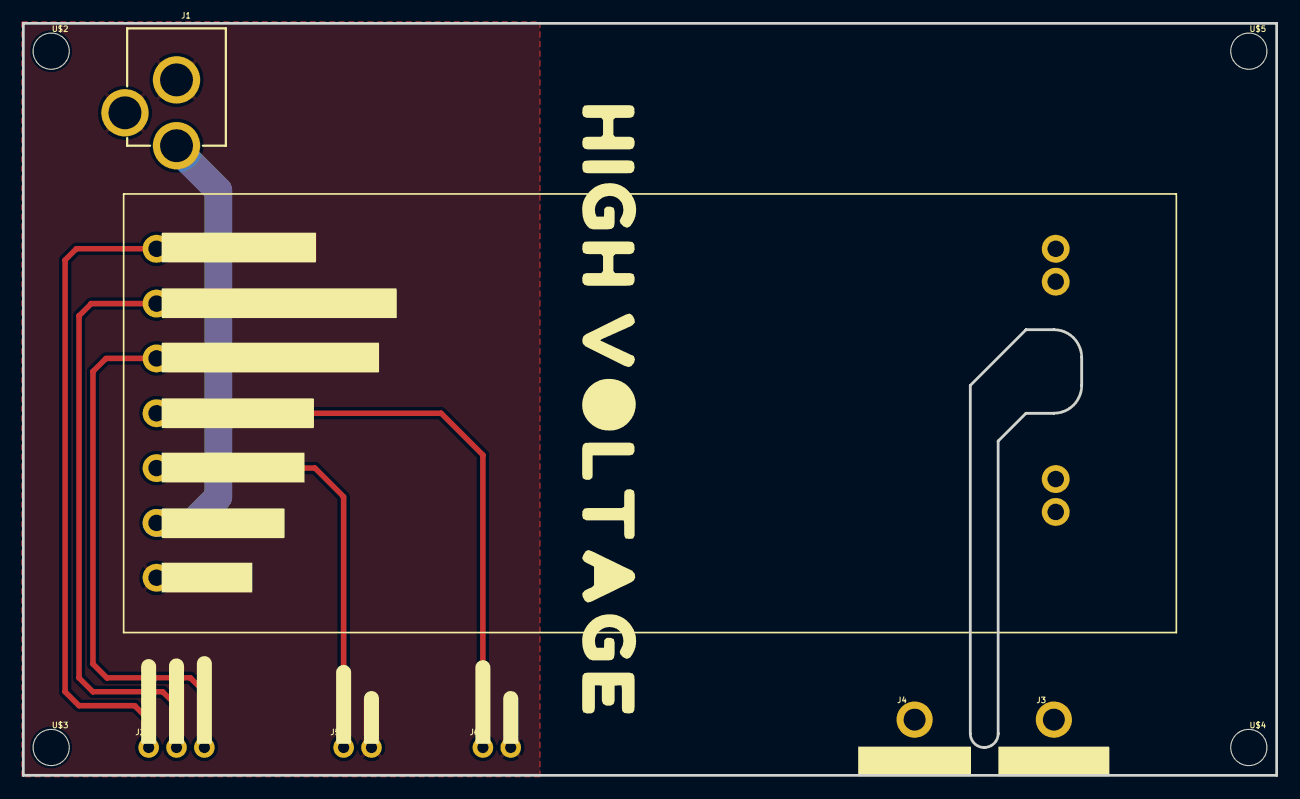
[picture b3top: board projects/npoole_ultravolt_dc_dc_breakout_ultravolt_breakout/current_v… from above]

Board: 2 copper layers, 114.3 x 68.6 mm, 28 parts (0 on the bottom side), 9 nets.

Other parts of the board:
U$2, U$3, U$4, U$5: STAND-OFF
U$6: HIGH_VOLTAGE0
U$7: #_#5V_REF#0
U$8: #_REMOTE_ADJ#0
U$9: #_SIGNAL_GND#0
U$10: #_ENABLE#0
U$11: #_I_SENSE#0
U$12: #_12V_IN#0
U$13: #_GND#0
U$14: #_#5V_REF_#0
U$15: #_ADJUST_#0
U$16: #HV_N#0
U$17: #HV_P#0
U$18: #_REF_GND_#0
U$19: #_I_SENSE_#0
U$20: #_ENABLE_#0
U$21, U$22: #_GND_#0

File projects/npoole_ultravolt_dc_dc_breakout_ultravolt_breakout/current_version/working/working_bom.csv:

"Id";"Designator";"Footprint";"Quantity";"Designation";"Supplier and ref";
1;"U$1";"ULTRAVOLT";1;"1A12-P4_M";;;
2;"U$21,U$22";"#_GND_#0";2;"";;;
3;"U$12";"#_12V_IN#0";1;"";;;
4;"J3,J4";"1X01_2MM";2;"";;;
5;"U$14";"#_#5V_REF_#0";1;"";;;
6;"J2";"1X03_NO_SILK";1;"";;;
7;"U$13";"#_GND#0";1;"";;;
8;"U$20";"#_ENABLE_#0";1;"";;;
9;"U$3,U$4,U$2,U$5";"STAND-OFF";4;"";;;
10;"U$7";"#_#5V_REF#0";1;"";;;
11;"U$17";"#HV_P#0";1;"";;;
12;"J1";"POWER_JACK_PTH";1;"POWER_JACK";;;
13;"U$8";"#_REMOTE_ADJ#0";1;"";;;
14;"U$19";"#_I_SENSE_#0";1;"";;;
15;"U$10";"#_ENABLE#0";1;"";;;
16;"U$15";"#_ADJUST_#0";1;"";;;
17;"U$11";"#_I_SENSE#0";1;"";;;
18;"U$16";"#HV_N#0";1;"";;;
19;"J5,J6";"1X02_NO_SILK";2;"";;;
20;"U$9";"#_SIGNAL_GND#0";1;"";;;
21;"U$6";"HIGH_VOLTAGE0";1;"";;;
22;"U$18";"#_REF_GND_#0";1;"";;;

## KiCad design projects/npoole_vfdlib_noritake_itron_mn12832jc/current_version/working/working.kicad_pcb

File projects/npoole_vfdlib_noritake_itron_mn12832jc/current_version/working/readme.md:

# vfdlib
 
## summary 
* id: npoole_vfdlib_noritake_itron_mn12832jc
* user: npoole
* name: vfdlib
* board: noritake_itron_mn12832jc
* repo: https://github.com/NPoole/VFDLib

* src_file_repo_sch: 
* src_file_repo_sch_link: https://github.com/NPoole/VFDLib/tree/main/
* full details link: https://github.com/oomlout/oomlout_oomp_project_bot_v_2/tree/main/projects/npoole_vfdlib_noritake_itron_mn12832jc/current_version/working  

## schematic  
  
[schematic (pdf)](working_schematic.pdf) 

## pcb  

[board (pdf)](working.pdf)  

## working_bom
| Id | Designator | Footprint | Quantity | Designation | Supplier and ref |  | None | 
| --- | --- | --- | --- | --- | --- | --- | --- | 
| 1 | U$18 | #_TXO#0 | 1 |  |  |  | [''] | 
| 2 | CCOMP0 | 0805 | 1 | 330pF |  |  | [''] | 
| 3 | R7,R14,R13 | 0603 | 3 | 22Î© |  |  | [''] | 
| 4 | F1 | 1210 | 1 | 6V/2A |  |  | [''] | 
| 5 | C8,C9 | 0603 | 2 | 22pF |  |  | [''] | 
| 6 | COUT0 | SM_RADIAL_J16 | 1 | EEV-FK2A151M |  |  | [''] | 
| 7 | C12,C6,C7,C2,C11 | 0603 | 5 | 0.1uF |  |  | [''] | 
| 8 | U$15,U$7 | #GND#0 | 2 |  |  |  | [''] | 
| 9 | U2 | 21-0041B_8_MXM | 1 | MAX628CSA+ |  |  | [''] | 
| 10 | C4,C5 | 0603 | 2 | 1nF |  |  | [''] | 
| 11 | IC1 | SOIC127P600X175-16N | 1 | CD74HC123ME4 |  |  | [''] | 
| 12 | J1,J2 | 1X04_NO_SILK | 2 |  |  |  | [''] | 
| 13 | U$3 | BLUESHIRE_SILK#SVG0 | 1 |  |  |  | [''] | 
| 14 | S1 | TACTILE_SWITCH_SMD_4.6X2.8MM | 1 | Reset |  |  | [''] | 
| 15 | U$16 | #_RXI#0 | 1 |  |  |  | [''] | 
| 16 | R6,R2,R5 | 0603 | 3 | 100k |  |  | [''] | 
| 17 | U$10,U$12 | #_5VDC#0 | 2 |  |  |  | [''] | 
| 18 | U$8 | #_SCL#0 | 1 |  |  |  | [''] | 
| 19 | CCOMP2 | 0805 | 1 | 82pF |  |  | [''] | 
| 20 | Q1 | SOT23-3 | 1 | 220mA/50V/3.5Î© |  |  | [''] | 
| 21 | CBYP0 | 0805 | 1 | 100nF |  |  | [''] | 
| 22 | U$14 | IND_NPI54C | 1 | 39uH |  |  | [''] | 
| 23 | R3,R8,RFB1,R9,R4 | 0603 | 5 | 10k |  |  | [''] | 
| 24 | U$6 | FOR_NORITAKE_ITRON_MN12832JC0 | 1 |  |  |  | [''] | 
| 25 | J3 | 2X3 | 1 | AVR_SPI_PROG_3X2PTH |  |  | [''] | 
| 26 | C3 | 0603 | 1 | 4.7uF |  |  | [''] | 
| 27 | RCOMP0 | 0603 | 1 | 332k |  |  | [''] | 
| 28 | RFILT0,R1 | 0603 | 2 | 100 |  |  | [''] | 
| 29 | U$11 | PG-TDSON-8 | 1 | 100V |  |  | [''] | 
| 30 | FRAME1 | DUMMY | 1 | FRAME-LEDGERNO_FOOTPRINT |  |  | [''] | 
| 31 | U$5 | OPEN_SOURCE_HARDWARE_DRIVER0 | 1 |  |  |  | [''] | 
| 32 | U1 | TSOT-23_6_ADI | 1 | LTC6906CS6TRPBF |  |  | [''] | 
| 33 | Q2 | TO-252_DPAK | 1 | 20A/100V/110mÎ© |  |  | [''] | 
| 34 | RSYNC0 | 0603 | 1 | 26.1k |  |  | [''] | 
| 35 | CFILT0 | 0603 | 1 | 10pF |  |  | [''] | 
| 36 | Y1 | CRYSTAL-SMD-5X3.2-4PAD | 1 | 16MHz |  |  | [''] | 
| 37 | U$4 | BLUESHIRE_STOP#SVG2 | 1 |  |  |  | [''] | 
| 38 | CIN0 | SM_RADIAL_C | 1 | 22uF |  |  | [''] | 
| 39 | RSENSE0 | 0603 | 1 | 50m |  |  | [''] | 
| 40 | U3 | TQFP44 | 1 | 32U4 |  |  | [''] | 
| 41 | R11,R12 | 0603 | 2 | 5.1k |  |  | [''] | 
| 42 | U4 | SOT353 | 1 | SN74LVC1G32DCKR |  |  | [''] | 
| 43 | U$9 | #_SDA#0 | 1 |  |  |  | [''] | 
| 44 | U$13 | SOD-123 | 1 | CDBW46-G |  |  | [''] | 
| 45 | C10,C13,C1 | 0603 | 3 | 1.0uF |  |  | [''] | 
| 46 | C14 | 0603 | 1 | 10nF |  |  | [''] | 
| 47 | RFB2 | 0603 | 1 | 464k |  |  | [''] | 
| 48 | U$2 | BLUESHIRE_COPPER#SVG1 | 1 |  |  |  | [''] | 
| 49 | U$1 | MUA08A | 1 | LM3488MM/NOPB |  |  | [''] | 
| 50 | J5 | USB-C-16P-5 | 1 |  |  |  | [''] | 
| 51 | U$17 | NORITAKE_ITRON_128X32 | 1 | NORITAKE_ITRON_128X32 |  |  | [''] | 

## bom_schematic
| Ref | Qnty | Value | Cmp name | Footprint | Description | Vendor | DNP | 
| --- | --- | --- | --- | --- | --- | --- | --- | 
| C1, C10, C13 | 3 | 1.0UF-0603-16V-10% | 1.0UF-0603-16V-10% | working:0603 |  |  |  | 
| C2, C7, C11, C12 | 4 | 0.1UF-0603-25V-(+80/-20%) | 0.1UF-0603-25V-(+80/-20%) | working:0603 |  |  |  | 
| C3 | 1 | 4.7UF-0603-35V-(20%) | 4.7UF-0603-35V-(20%) | working:0603 |  |  |  | 
| C4, C5 | 2 | 1nF | 1.0NF/1000PF-0603-50V-10% | working:0603 |  |  |  | 
| C6 | 1 | 0.1UF-0603-100V-10% | 0.1UF-0603-100V-10% | working:0603 |  |  |  | 
| C8, C9 | 2 | 22PF-0603-50V-5% | 22PF-0603-50V-5% | working:0603 |  |  |  | 
| C14 | 1 | 10NF-0603-50V-10% | 10NF-0603-50V-10% | working:0603 |  |  |  | 
| CBYP0 | 1 | CL21C100JBANNNC | CL21C100JBANNNC | working:0805 |  |  |  | 
| CCOMP0 | 1 | CL21C331JBANNNC | CL21C331JBANNNC | working:0805 |  |  |  | 
| CCOMP2 | 1 | CL21C820JBANNNC | CL21C820JBANNNC | working:0805 |  |  |  | 
| CFILT0 | 1 | GRM188R70J104KA01D | GRM188R70J104KA01D | working:0603 |  |  |  | 
| CIN0 | 1 | EEE-FK1C220R | EEE-FK1C220R | working:SM_RADIAL_C |  |  |  | 
| COUT0 | 1 | EEV-FK2A151M | EEV-FK2A151M | working:SM_RADIAL_J16 |  |  |  | 
| F1 | 1 | PPTC_6V2A | PPTC_6V2A | working:1210 |  |  |  | 
| FRAME1 | 1 | FRAME-LEDGERNO_FOOTPRINT | FRAME-LEDGERNO_FOOTPRINT | working:DUMMY |  |  |  | 
| IC1 | 1 | CD74HC123ME4 | CD74HC123ME4 | working:SOIC127P600X175-16N |  |  |  | 
| J1, J2 | 2 | CONN_041X04_NO_SILK | CONN_041X04_NO_SILK | working:1X04_NO_SILK |  |  |  | 
| J3 | 1 | AVR_SPI_PROG_3X2PTH | AVR_SPI_PROG_3X2PTH | working:2X3 |  |  |  | 
| J5 | 1 | USB_C5 | USB_C5 | working:USB-C-16P-5 |  |  |  | 
| Q1 | 1 | MOSFET-NCH-BSS138 | MOSFET-NCH-BSS138 | working:SOT23-3 |  |  |  | 
| Q2 | 1 | MOSFET_PCH-MCU20P10 | MOSFET_PCH-MCU20P10 | working:TO-252_DPAK |  |  |  | 
| R1 | 1 | 100OHM-0603-1/10W-1% | 100OHM-0603-1/10W-1% | working:0603 |  |  |  | 
| R2, R5, R6 | 3 | 100KOHM-0603-1/10W-1% | 100KOHM-0603-1/10W-1% | working:0603 |  |  |  | 
| R3, R4, R8, R9 | 4 | 10KOHM-0603-1/10W-1% | 10KOHM-0603-1/10W-1% | working:0603 |  |  |  | 
| R7, R13, R14 | 3 | 22OHM-0603-1/10W-1% | 22OHM-0603-1/10W-1% | working:0603 |  |  |  | 
| R11, R12 | 2 | 5.1k | 5.1KOHM5.1KOHM-0603-1/10W-1% | working:0603 |  |  |  | 
| RCOMP0 | 1 | CRCW0603332KFKEA | CRCW0603332KFKEA | working:0603 |  |  |  | 
| RFB1 | 1 | CRCW060310K0FKEA | CRCW060310K0FKEA | working:0603 |  |  |  | 
| RFB2 | 1 | RC0603FR-07464KL | RC0603FR-07464KL | working:0603 |  |  |  | 
| RFILT0 | 1 | CRCW0603100RFKEA | CRCW0603100RFKEA | working:0603 |  |  |  | 
| RSENSE0 | 1 | ERJ-L03KF50MV | ERJ-L03KF50MV | working:0603 |  |  |  | 
| RSYNC0 | 1 | RC0603FR-0726K1L | RC0603FR-0726K1L | working:0603 |  |  |  | 
| S1 | 1 | MOMENTARY-SWITCH-SPST-SMD-4.6X2.8MM | MOMENTARY-SWITCH-SPST-SMD-4.6X2.8MM | working:TACTILE_SWITCH_SMD_4.6X2.8MM |  |  |  | 
| U1 | 1 | LTC6906CS6TRPBF | LTC6906CS6TRPBF | working:TSOT-23_6_ADI |  |  |  | 
| U2 | 1 | MAX628CSA+ | MAX628CSA+ | working:21-0041B_8_MXM |  |  |  | 
| U3 | 1 | ATMEGA32U4TQFP-44 | ATMEGA32U4TQFP-44 | working:TQFP44 |  |  |  | 
| U4 | 1 | SN74LVC1G32DCKR | 7432 | working:SOT353 |  |  |  | 
| U$1 | 1 | LM3488MM/NOPB | LM3488MM/NOPB | working:MUA08A |  |  |  | 
| U$11 | 1 | BSC265N10LSF_G | BSC265N10LSF_G | working:PG-TDSON-8 |  |  |  | 
| U$13 | 1 | CDBW46-G | CDBW46-G | working:SOD-123 |  |  |  | 
| U$14 | 1 | NPI54C390KTRF | NPI54C390KTRF | working:IND_NPI54C |  |  |  | 
| U$17 | 1 | NORITAKE_ITRON_128X32 | NORITAKE_ITRON_128X32 | working:NORITAKE_ITRON_128X32 |  |  |  | 
| Y1 | 1 | 16MHz | CRYSTAL-16MHZSMD-5X3.2 | working:CRYSTAL-SMD-5X3.2-4PAD |  |  |  |

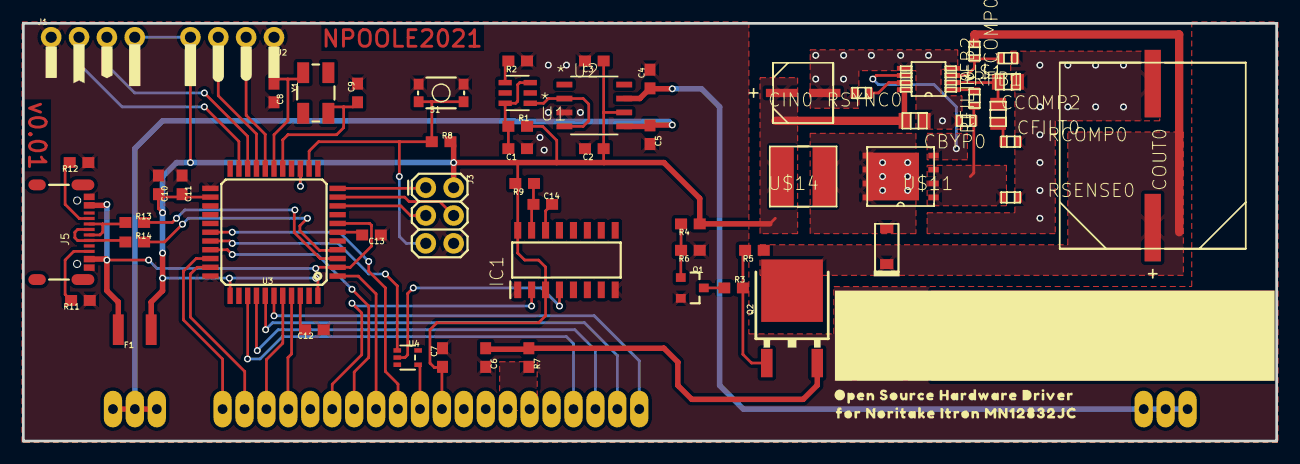
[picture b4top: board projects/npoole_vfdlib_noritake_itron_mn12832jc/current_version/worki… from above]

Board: 2 copper layers, 114.3 x 38.1 mm, 72 parts (1 on the bottom side), 57 nets.

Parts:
C1, C10, C13: 1.0uF; 0603
C2, C6, C7, C11, C12: 0.1uF; 0603
C3: 4.7uF; 0603
C4, C5: 1nF; 0603
C8, C9: 22pF; 0603
C14: 10nF; 0603
CBYP0: 100nF; 0805
CCOMP0: 330pF; 0805
CCOMP2: 82pF; 0805
CFILT0: 10pF; 0603
CIN0: 22uF; SM_RADIAL_C
COUT0: EEV-FK2A151M; SM_RADIAL_J16
F1: 6V/2A; 1210
FRAME1: FRAME-LEDGERNO_FOOTPRINT; DUMMY
IC1: CD74HC123ME4; SOIC127P600X175-16N
J1, J2: 1X04_NO_SILK
J3: AVR_SPI_PROG_3X2PTH; 2X3
J5: USB-C-16P-5
Q1: 220mA/50V/3.5Ω; SOT23-3
Q2: 20A/100V/110mΩ; TO-252_DPAK
R1: 100; 0603
R2, R5, R6: 100k; 0603
R3, R4, R8, R9: 10k; 0603
R7, R13, R14: 22Ω; 0603
R11, R12: 5.1k; 0603
RCOMP0: 332k; 0603
RFB1: 10k; 0603
RFB2: 464k; 0603
RFILT0: 100; 0603
RSENSE0: 50m; 0603
RSYNC0: 26.1k; 0603
S1: Reset; TACTILE_SWITCH_SMD_4.6X2.8MM
U1: LTC6906CS6TRPBF; TSOT-23_6_ADI
U2: MAX628CSA+; 21-0041B_8_MXM
U3: 32U4; TQFP44
U4: SN74LVC1G32DCKR; SOT353
U$1: LM3488MM/NOPB; MUA08A
U$2: BLUESHIRE_COPPER#SVG1
U$3: BLUESHIRE_SILK#SVG0
U$4: BLUESHIRE_STOP#SVG2
U$5: OPEN_SOURCE_HARDWARE_DRIVER0
U$6: FOR_NORITAKE_ITRON_MN12832JC0
U$7, U$15: #GND#0
U$8: #_SCL#0
U$9: #_SDA#0
U$10, U$12: #_5VDC#0
U$11: 100V; PG-TDSON-8
U$13: CDBW46-G; SOD-123
U$14: 39uH; IND_NPI54C
U$16: #_RXI#0
U$17: NORITAKE_ITRON_128X32
U$18: #_TXO#0
Y1: 16MHz; CRYSTAL-SMD-5X3.2-4PAD

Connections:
5V: C2.1, C3.1, C7.1, C10.2, C11.2, CBYP0.1, CIN0.1, F1.1, IC1.3, IC1.16, J1.4, J2.4, J3.2, R1.2, R4.1, R8.2, R9.2, U2.6, U3.14, U3.24, U3.34, U3.44, U$1.8, U$14.1, U$17.P$13
60V: COUT0.1, Q2.2, R5.1, RFB2.2, U$13.1
100KHZ: U1.1, U2.2, U2.4
AREF: C12.2, U3.42
BLK1: U3.39, U$17.P$4
BLK2: U3.31, U$17.P$23
CIPO: J3.1, U3.11
CLK1: U3.37, U$17.P$6
CLK2: U3.40, U$17.P$21
COPI: J3.4, U3.10
D-_HV: J5.A7, J5.B7, R13.1
DP_HV: J5.A6, J5.B6, R14.1
D_N: R13.2, U3.3
D_P: R14.2, U3.4
F1_DRIVE: C4.1, U2.7, U$17.P$1, U$17.P$2, U$17.P$3
F2_DRIVE: C5.1, U2.5, U$17.P$26, U$17.P$27, U$17.P$28
GBLK: U4.4, U$17.P$14
GBLK_OR_IN: U3.29, U4.1
GCLK: U3.1, U$17.P$16
GLAT: U3.28, U$17.P$15
GND: C1.1, C2.2, C3.2, C4.2, C5.2, C6.2, C7.2, C8.2, C9.2, C10.1, C11.1, C12.1, C13.1, CBYP0.2, CCOMP2.2, CFILT0.2, CIN0.2, COUT0.2, IC1.1, IC1.8, J1.1, J2.1, J3.6, J5.GND, J5.GND2, Q1.2, R2.1, R6.1, R11.1, R12.1, RCOMP0.1, RFB1.2, RSENSE0.1, RSYNC0.1, S1.1, S1.2, U1.2, U2.3, U3.5, U3.15, U3.23, U3.33, U3.35, U3.43, U$1.4, U$1.5, U$17.P$11, U$17.P$12
GSIN: U3.30, U$17.P$17
GSOUT: IC1.2, U$17.P$18
LAT1: U3.38, U$17.P$5
LAT2: U3.32, U$17.P$22
unnamed: RSYNC0.2, U$1.7
unnamed: CCOMP0.1, CCOMP2.1, U$1.2
unnamed: RFILT0.2, U$1.1
unnamed: CCOMP0.2, RCOMP0.2
unnamed: CFILT0.1, RFILT0.1, RSENSE0.2, U$11.1, U$11.2, U$11.3
unnamed: U$11.5, U$11.6, U$11.7, U$11.8, U$11.9, U$13.2, U$14.2
unnamed: RFB1.1, RFB2.1, U$1.3
unnamed: U$1.6, U$11.4
unnamed: C1.2, R1.1, U1.3, U1.6
unnamed: R2.2, U1.4
unnamed: R7.2, U$17.P$9, U$17.P$10
unnamed: Q1.1, R4.2, R6.2
unnamed: Q1.3, R3.1
unnamed: Q2.1, R3.2, R5.2
unnamed: C9.1, U3.16, Y1.1
unnamed: C8.1, U3.17, Y1.3
unnamed: C14.2, IC1.14
unnamed: C14.1, IC1.15, R9.1
unnamed: J5.A5, R12.2
unnamed: J5.B5, R11.2
RESET: J3.5, R8.1, S1.3, S1.4, U3.13
RXI: J1.3, U3.20
SCK: J3.3, U3.9
SCL: J2.2, U3.18
SDA: J2.3, U3.19
SIN1: U3.36, U$17.P$7
SIN2: U3.41, U$17.P$20
TXO: J1.2, U3.21
UCAP: C13.2, U3.6
VDD2: C6.1, Q2.3, R7.1
V_USB: F1.2, J5.VBUS1, J5.VBUS2, U3.2, U3.7
WATCHDOG: IC1.4, U4.2

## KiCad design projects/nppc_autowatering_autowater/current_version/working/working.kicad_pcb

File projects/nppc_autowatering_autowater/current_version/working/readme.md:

# autowatering
 
## summary 
* id: nppc_autowatering_autowater
* user: nppc
* name: autowatering
* board: autowater
* repo: https://github.com/nppc/AutoWatering
* src_file_repo_kicad_pcb: KiCad/AutoWater/AutoWater.kicad_pcb
* src_file_repo_kicad_pcb_link: https://github.com/nppc/AutoWatering/tree/master/KiCad/AutoWater/AutoWater.kicad_pcb

* src_file_repo_sch: KiCad/AutoWater/AutoWater.sch
* src_file_repo_sch_link: https://github.com/nppc/AutoWatering/tree/master/KiCad/AutoWater/AutoWater.sch
* full details link: https://github.com/oomlout/oomlout_oomp_project_bot_v_2/tree/main/projects/nppc_autowatering_autowater/current_version/working

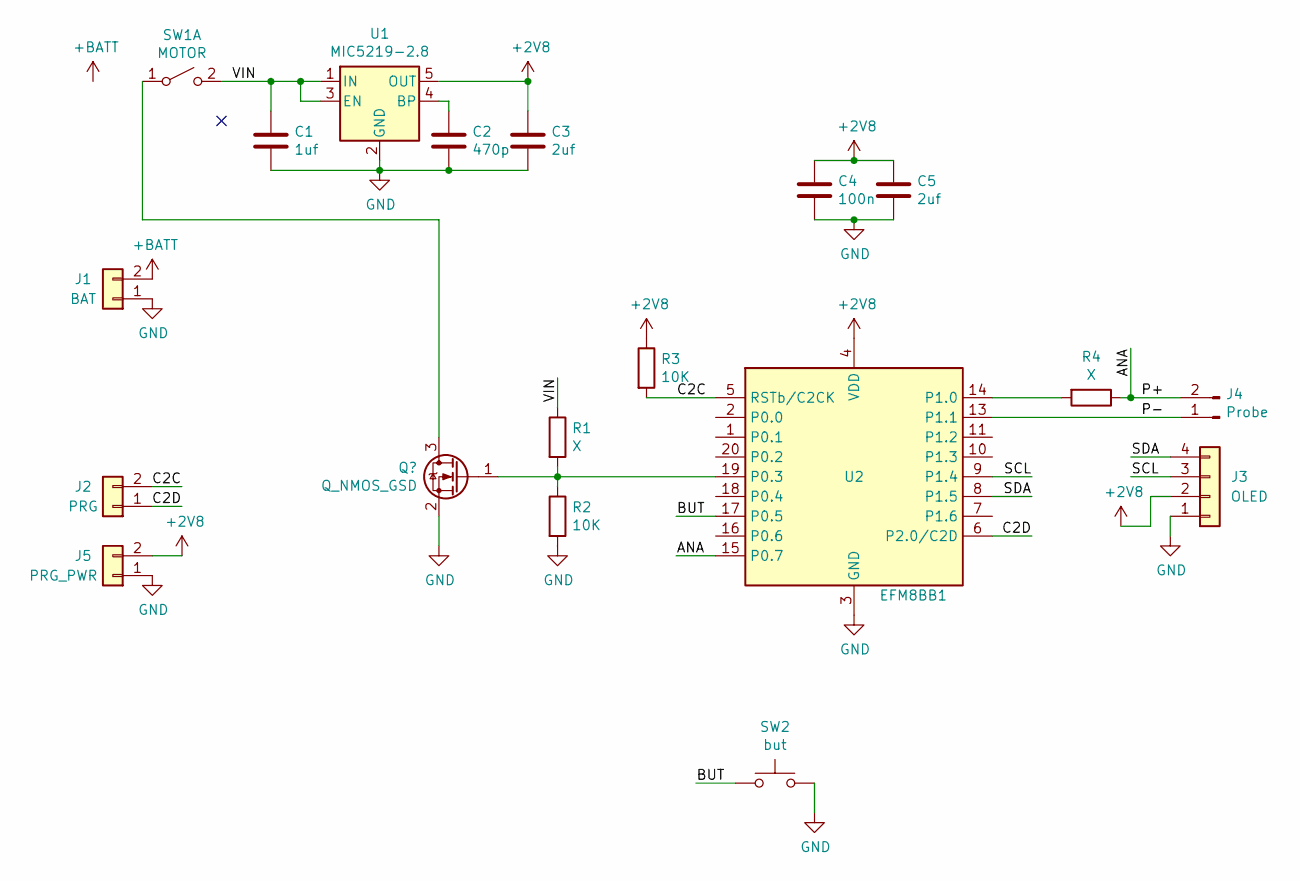
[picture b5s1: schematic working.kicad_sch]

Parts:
C1: 1uf; C_0603
C2: 470p; C_0603
C3, C5: 2uf; C_0603
C4: 100n; C_0603
J1: BAT; Conn_1x02_2.54_0.9mm
J2: PRG; POWER2PIN_2
J3: OLED; Pin_Header_Straight_1x04_Pitch2.54mm
J4: Probe; POWER2PIN_2
J5: PRG_PWR; POWER2PIN_2
R1, R4: X; R_0603
R2, R3: 10K; R_0603
SW1: MOTOR; Conn_1x02_2.54_0.9mm
SW2: but; POWER2PIN_2
U1: MIC5219-2.8; SOT-23-5
U2: EFM8BB1; QFN20

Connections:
+2V8: C3.1, C4.1, C5.1, J3.2, J5.2, R3.1, U1.5 (OUT), U2.4 (VDD)
+BATT: J1.2, SW1.1 (A)
/ANA: J4.2, R4.1, U2.15 (P0.7)
/BUT: SW2.1, U2.17 (P0.5)
/C2C: J2.2, R3.2, U2.5 (RSTb/C2CK)
/C2D: J2.1, U2.6 (P2.0/C2D)
/P-: J4.1, U2.13 (P1.1)
/SCL: J3.3, U2.9 (P1.4)
/SDA: J3.4, U2.8 (P1.5)
/VIN: C1.1, R1.1, SW1.2 (B), U1.1 (IN), U1.3 (EN)
GND: C1.2, C2.2, C3.2, C4.2, C5.2, J1.1, J3.1, J5.1, R2.2, SW2.2, U1.2 (GND), U2.3 (GND), U2.12 (GND), U2.21 (GND)
unnamed: C2.1, U1.4 (BP)
unnamed: R1.2, R2.1, U2.19 (P0.3)
unnamed: R4.2, U2.14 (P1.0)

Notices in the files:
projects/npoole_mldca201_mldca201/current_version/working/working.kicad_sch:
https://creativecommons.org/licenses/by-sa/4.0
Released under the Creative Commons
parts and their libraries:
Released under the Creative Commons Attribution Share-Alike 4.0 License
